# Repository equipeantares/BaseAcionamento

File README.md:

# Base de Acionamento

## Introdução 

### Motivação

A equipe Antares de espaçomodelismo da Unicamp tem como um de seus projetos desenvolvidos o foguete Aurora. Trata-se de um foguete de propulsão sólida com apogeu esperado de 3km. Como parte dos requisitos necessários para ter sucesso na missão, o foguete precisa de um sistema de aviônica que será responsável por coletar dados e tomar decisões previamente programadas durante o voo. Com o objetivo de monitorar o estado do foguete antes, durante e depois do lançamento, é necessário ter um sistema em solo que seja capaz de receber os dados coletados pela aviônica, permitindo que os presentes tenham informações em tempo real. Além disso, esse sistema deve permitir que o acionador do motor seja ligado de forma segura durante o lançamento, não expondo pessoas a riscos.

### Objetivo

Sendo assim, o objetivo deste projeto é desenvolver um sistema de controle de base para o foguete, o qual deve ser capaz de iniciar o lançamento de forma segura e robusta e capaz de receber e apresentar dados da telemetria do voo colhidos pela aviônica.

### Soluções comerciais

Pelo fato de o sistema precisar ser personalizado, se ajustando ao sistema presente no foguete e aos demais requisitos específicos do projeto, não existem alternativas comerciais que cumpram integralmente o objetivo.

## Especificação
    - Microcontrolador: o dispositivo deverá ser capaz de fazer processamentos lógicos, sendo assim necessário um microcontrolador. Por motivos de acessibilidade e familiaridade, será utilizada a plataforma Arduino no MCU ESP-8266 12F.

    - Comunicação e dados: com o objetivo de receber dados de telemetria do foguete, o dispositivo deverá ter um sistema transceptor, que será implementado por um módulo LoRA E32-915T20D.

    - Interface: como interface, o dispositivo contará com pinos auxiliares para monitoramento do funcionamento da placa e pinos de seleção de função para alimentação e modo de acionamento da ignição, sendo a seleção feita por meio de jumpers.

    - Ignição: deverá suportar dois modos de acionamento do circuito ignitor: por sinal elétrico e por comando remoto. O modo será escolhido via inserção manual de jumpers antes do lançamento.

    - Alimentação: o sistema deverá ter interface de alimentação, podendo operar com a alimentação interna de 3V3 ou alimentação externa de 5V.

## Diagrama

## Pinagem

### Pinout conector Screw bateria 18650

Pino | Sinal
-----|------
1  | VBat
2  | GND

### Pinout conector Screw do Acionamento

Pino | Sinal
-----|------
  1  | NiCr_ISO
  2  | GND_ISO

### Pinout conector Screw Alimentação externa

Pino | Sinal
-----|------
  1  | VExt
  2  | GND

### Pinout conector GPIO aux

Pino | Sinal
-----|------
  1  | DIO1
  2  | DIO2
  3  | 3V3
  4  | GND

### Pinout conector LoRA aux

Pino | Sinal
-----|------
  1  | OutputLora
  2  | InputLora
  3  | 3V3
  4  | GND

### Pinout conector I2C aux

Pino | Sinal
-----|------
  1  | SCL_SLAVE
  2  | SDA_SLAVE
  3  | 3V3
  4  | GND

### Pinout conector SPI aux

Pino | Sinal
-----|------
  1  | MOSI
  2  | CS
  3  | MISO
  4  | SCLK
  5  | GND

### Pinout conector de seleção alimentação LoRA

Pino | Sinal
-----|------
  1  | 3V3
  2  | VLora
  3  | VExt

### Pinout conector Transistor PNP acionamento (interno)

Pino | Sinal
-----|------
  1  | Emissor
  2  | Coletor

### Pinout conector Optoacoplador acionamento (externo)

Pino | Sinal
-----|------
  1  | Coletor
  2  | Emissor

## Testes

    A fim de garantir que o sistema seja seguro e que tudo funcione como esperado, é necessário realizar testes controlados de cada parte do sistema, tentando antecipar possíveis falhas que possam ocorrer. 
    Como o sistema de ignição não pode ter acionamento indesejado, devem ocorrer testes em ambientes adversos, como, por exemplo, com componentes desconectados, e o resultado esperado é que o sistema não ative em nenhuma dessas situações.

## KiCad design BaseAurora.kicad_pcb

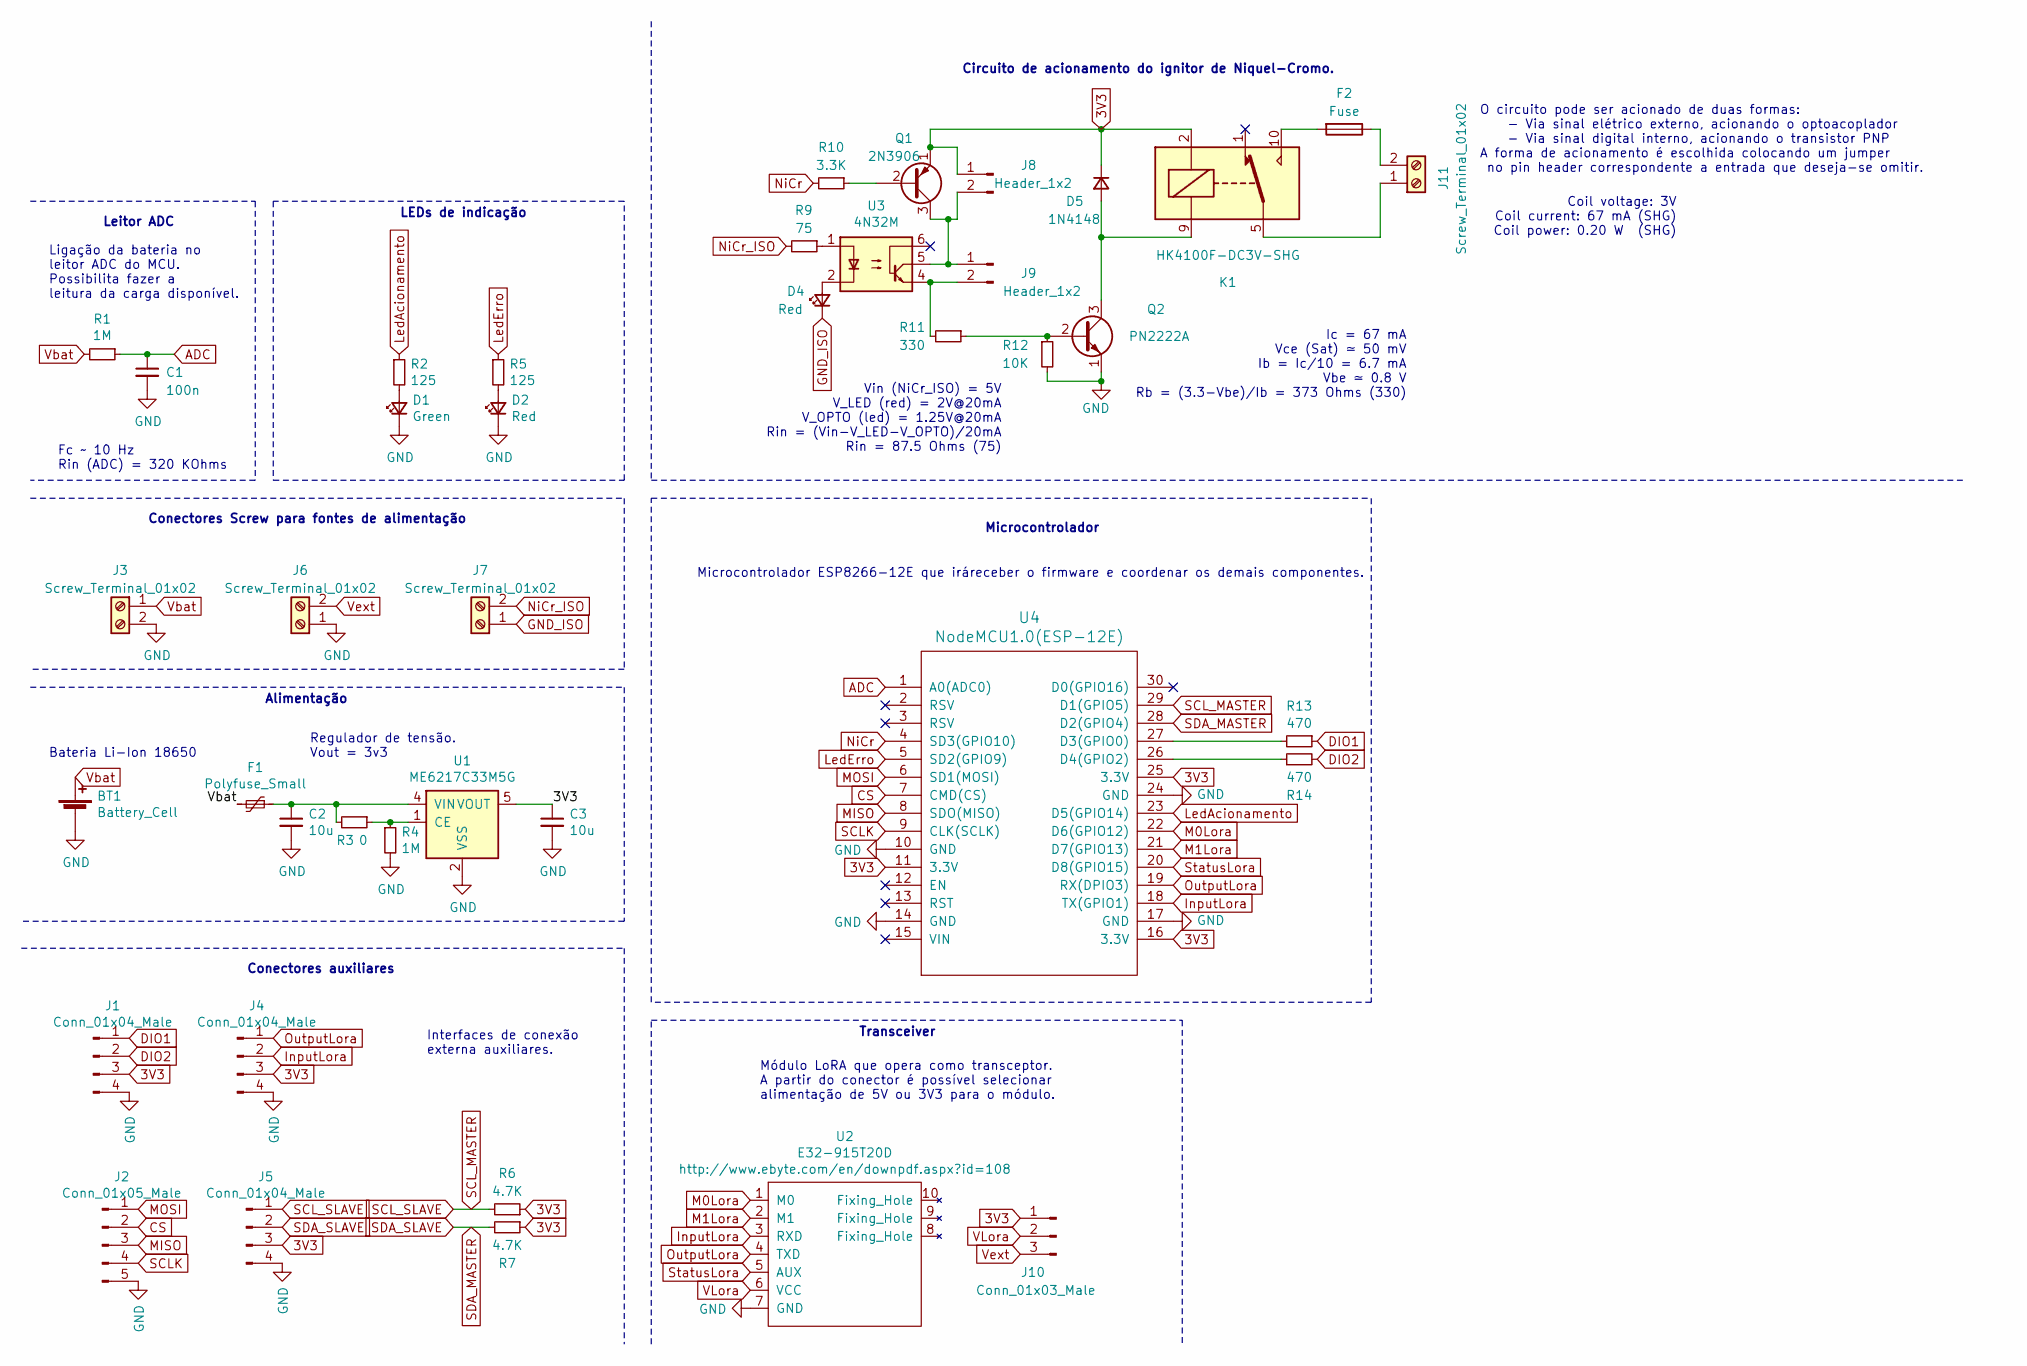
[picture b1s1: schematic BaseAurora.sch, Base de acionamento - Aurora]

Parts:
BT1: Battery_Cell; BatteryHolder_Keystone_1042_1x18650
C1: 100n; C_0805_2012Metric
C2, C3: 10u; C_0805_2012Metric
D1: Green; LED_D3.0mm_Horizontal_O1.27mm_Z2.0mm
D2, D4: Red; LED_D3.0mm_Horizontal_O1.27mm_Z2.0mm
D5: 1N4148; D_SOD-123
F1: Polyfuse_Small; Fuse_1206_3216Metric_Castellated
F2: Fuse; Fuseholder_Cylinder-5x20mm_Stelvio-Kontek_PTF78_Horizontal_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
J1, J4, J5: Conn_01x04_Male; Molex_KK-254_AE-6410-04A_1x04_P2.54mm_Vertical
J2: Conn_01x05_Male; Molex_KK-254_AE-6410-05A_1x05_P2.54mm_Vertical
J3, J6, J7, J11: Screw_Terminal_01x02; TerminalBlock_Phoenix_MKDS-1,5-2_1x02_P5.00mm_Horizontal
J8, J9: Header_1x2; Molex_KK-254_AE-6410-02A_1x02_P2.54mm_Vertical
J10: Conn_01x03_Male; Molex_KK-254_AE-6410-03A_1x03_P2.54mm_Vertical
K1: HK4100F-DC3V-SHG; Relay_SPDT_Omron_G5V-1
Q1: 2N3906; TO-92_Inline
Q2: PN2222A; TO-92_Inline
R1, R4: 1M; R_0805_2012Metric
R2, R5: 125; R_0805_2012Metric
R3: 0; R_0805_2012Metric
R6, R7: 4.7K; R_0805_2012Metric
R9: 75; R_0805_2012Metric
R10: 3.3K; R_0805_2012Metric
R11: 330; R_0805_2012Metric
R12: 10K; R_0805_2012Metric
R13, R14: 470; R_0805_2012Metric
U1: ME6217C33M5G; SOT-23-5
U2: E32-915T20D; E32-xxxT20D
U3: 4N32M; DIP-6_W7.62mm
U4: NodeMCU1.0(ESP-12E); ESP12F-Devkit-V3

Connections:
3V3: C3.1, D5.1 (K), J1.3, J4.3, J5.3, J8.1, J10.1, K1.2, Q1.1 (E), R6.1, R7.1, U1.5 (VOUT), U4.11 (3.3V), U4.16 (3.3V), U4.25 (3.3V)
ADC: C1.1, R1.1, U4.1 (A0(ADC0))
CS: J2.2, U4.7 (CMD(CS))
DIO1: J1.1, R13.1
DIO2: J1.2, R14.2
GND: BT1.2 (-), C1.2, C2.2, C3.2, D1.1 (K), D2.1 (K), J1.4, J2.5, J3.2, J4.4, J5.4, J6.1, Q2.1 (E), R4.2, R12.2, U1.2 (VSS), U2.7 (GND), U4.10 (GND), U4.14 (GND), U4.17 (GND), U4.24 (GND)
GND_ISO: D4.1 (K), J7.1
InputLora: J4.2, U2.3 (RXD), U4.18 (TX(GPIO1))
LedAcionamento: R2.1, U4.23 (D5(GPIO14))
LedErro: R5.1, U4.5 (SD2(GPIO9))
M0Lora: U2.1 (M0), U4.22 (D6(GPIO12))
M1Lora: U2.2 (M1), U4.21 (D7(GPIO13))
MISO: J2.3, U4.8 (SDO(MISO))
MOSI: J2.1, U4.6 (SD1(MOSI))
unnamed: C2.1, F1.1, R3.2, U1.4 (VIN)
unnamed: D1.2 (A), R2.2
unnamed: D2.2 (A), R5.2
unnamed: D4.2 (A), U3.2
unnamed: D5.2 (A), K1.9, Q2.3 (C)
unnamed: F2.1, J11.2
unnamed: F2.2, K1.10
unnamed: J8.2, J9.1, Q1.3 (C), U3.5
unnamed: J9.2, R11.2, U3.4
unnamed: J11.1, K1.5, K1.6
unnamed: Q1.2 (B), R10.1
unnamed: Q2.2 (B), R11.1, R12.1
unnamed: R3.1, R4.1, U1.1 (CE)
unnamed: R9.1, U3.1
unnamed: R13.2, U4.27 (D3(GPIO0))
unnamed: R14.1, U4.26 (D4(GPIO2))
NiCr: R10.2, U4.4 (SD3(GPIO10))
NiCr_ISO: J7.2, R9.2
OutputLora: J4.1, U2.4 (TXD), U4.19 (RX(DPIO3))
SCLK: J2.4, U4.9 (CLK(SCLK))
SCL_MASTER: J5.1, R6.2, U4.29 (D1(GPIO5))
SDA_MASTER: J5.2, R7.2, U4.28 (D2(GPIO4))
StatusLora: U2.5 (AUX), U4.20 (D8(GPIO15))
VLora: J10.2, U2.6 (VCC)
Vbat: BT1.1 (+), F1.2, J3.1, R1.2
Vext: J6.2, J10.3

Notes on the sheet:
Coil voltage: 3V Coil current: 67 mA (SHG) Coil power: 0.20 W (SHG)
Ic = 67 mA Vce (Sat) ≃ 50 mV Ib = Ic/10 = 6.7 mA Vbe ≃ 0.8 V Rb = (3.3-Vbe)/Ib = 373 Ohms (330)
Vin (NiCr_ISO) = 5V V_LED (red) = 2V@20mA V_OPTO (led) = 1.25V@20mA Rin = (Vin-V_LED-V_OPTO)/20mA Rin = 87.5 Ohms (75)
Fc ~~ 10 Hz Rin (ADC) = 320 KOhms
Interfaces de conexão externa auxiliares.
Regulador de tensão. Vout = 3v3
Conectores Screw para fontes de alimentação
LEDs de indicação
Ligação da bateria no leitor ADC do MCU. Possibilita fazer a leitura da carga disponível.
Módulo LoRA que opera como transceptor. A partir do conector é possível selecionar alimentação de 5V ou 3V3 para o módulo.
Microcontrolador ESP8266-12E que iráreceber o firmware e coordenar os demais componentes.
O circuito pode ser acionado de duas formas: - Via sinal elétrico externo, acionando o optoacoplador - Via sinal digital interno, acionando o transistor PNP A forma de acionamento é escolhida colocando um jumper no pin header correspondente a entrada que deseja-se omitir.
Circuito de acionamento do ignitor de Niquel-Cromo.
Microcontrolador
Transceiver
Conectores auxiliares
Bateria Li-Ion 18650
Alimentação
Leitor ADC

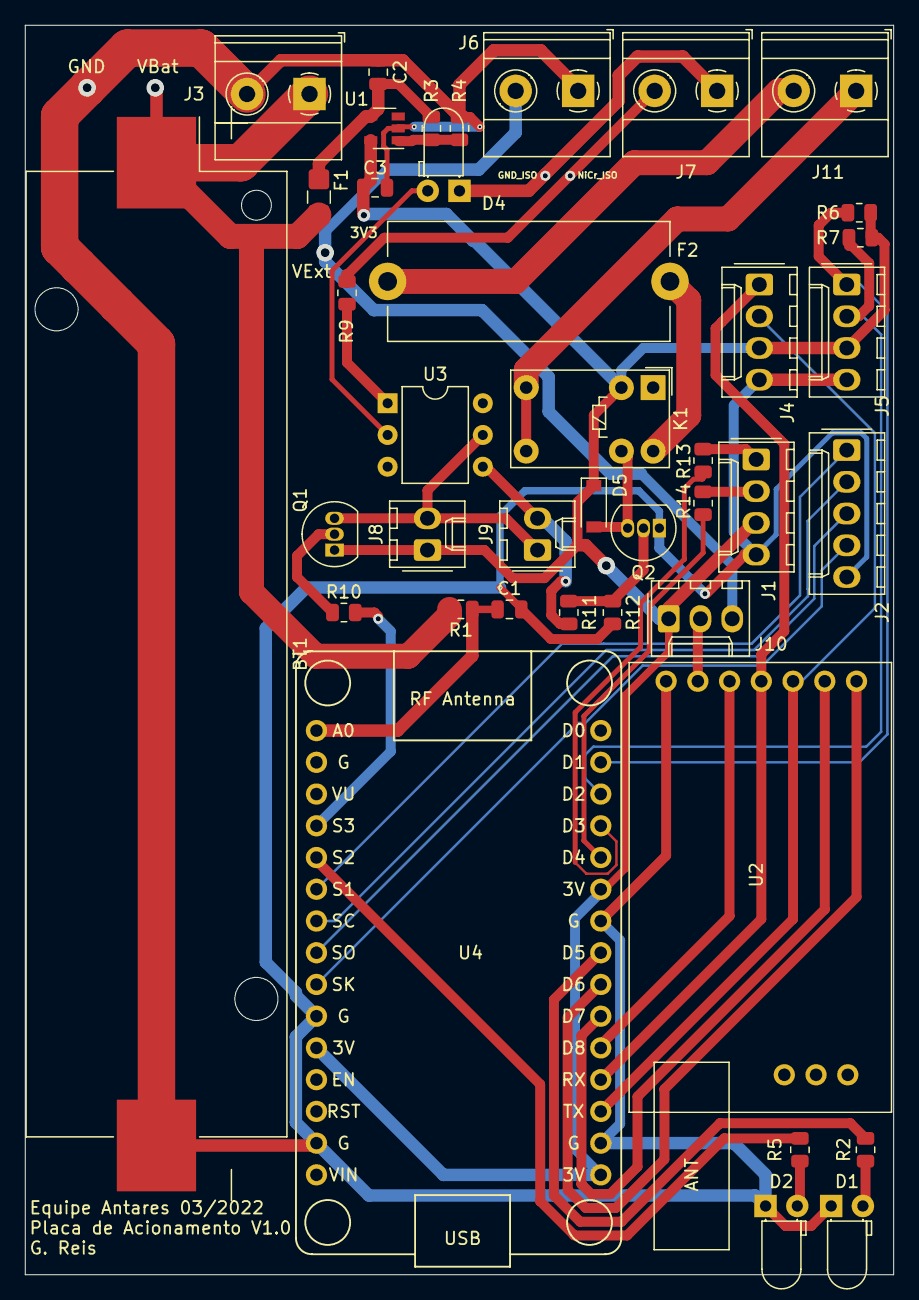
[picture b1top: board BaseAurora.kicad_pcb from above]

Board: 2 copper layers, 69.5 x 100.0 mm, 41 parts (0 on the bottom side), 40 nets.

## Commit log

2022-03-04 commit inicial
2022-03-08 esquematico revisado
2022-03-10 Revisão do circuito de acionamento. Atribuição de valores para os componentes. Organização geral do esquemático.
2022-03-11 Reorganização dos componentes e posicionamento do acionamento do NiCr no pino seguro.
2022-03-16 Design inicial da pcb
2022-03-18 Refatoração do component placement e design das tracks seguindo o novo fator de forma. Exclusão de um dos leds e reposicionamento da conexão NiCr.
2022-03-18 Adiciona silk com o logo da equipe
2022-03-21 Correção do design de acordo com o DRC
2022-03-22 Adiciona CSV da BOM e vias de test points
2022-03-23 Atualiza o README com as especificações do projeto
2022-03-23 Correcoes no markdown
2022-03-28 Arquivos finais para fabricação
2022-11-30 Separa os arquivos em hardware e firmware e adiciona o código do firmware
2022-11-30 adiciona \n após o s
